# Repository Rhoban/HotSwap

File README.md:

# Hot swap

This is a simple hot swap board for dynamixel

## Features

With this system, when a battery is plugged, the LOGIC (for instance the robot computer) is powered through a diode, allowing a second battery to be plugged simultaneously

The SPDT switch allow to choose which battery is powering the motors, allowing an hot swap of the battery with the following sequence:

* Plugging the second battery
* Switching the SPDT switch
* Unplugging the first battery

The robot's computer will not reboot and the motors are now powered by the new battery

## 3 buses wiring

This Dynamixel HUB features 8 connectors, which have the same power supply but separated buses, with purpose to be combined with triple buses [Rhoban DXLBoard](http://github.com/Rhoban/DXLBoard):

* 2 connectors for leg 1
    * One should be connected to the first bus of the DXLBoard
    * The other should be connected to the first motor of one leg (the other are daisy chained)
* 4 connectors for the torso
    * One is connected to the second bus of the DXLBoard
    * The second to the first motor of left shoulder
    * The third to the first motor of right shoulder
    * The last to the first motor of the head
* 2 connectors for leg 2
    * One is connected to the second bus of DXLBoard
    * The other is connected to the other leg first mother

Then, the motors should be dispatched on three separate bus, one for left leg, one for right leg and one for the upper body of the robot.

## Components

You can find all the required components in the ``BOM.xlsx`` file. Note that you should choose between 3 and 4 pins for your dynamixel connectors.

* Switch
    * https://fr.farnell.com/arcolectric/c1520ataaa/interrupteur-a-bascule-spdt-ctr/dp/150551
    * Farnell ref: 150551
    * Constructor ref: C1520ATAAA 
* Double diode
    * https://fr.farnell.com/on-semiconductor/mbr1545ctg/diode-schottky-15a-45v-to-220/dp/1431049
    * Farnell ref: 1431049
    * Constructor ref: MBR1545CTG
* Dynamixel MOLEX connectors
    * 3 pins: https://fr.farnell.com/molex/22-03-5035/embase-droite-2-5mm-3-voies/dp/9979620
    * Farnell ref: 9979620
    * Constructor ref: 22-03-5035 
    * 4 pins: https://fr.farnell.com/molex/22035045/embase-vertical-2-5mm-4-voies/dp/1104204
    * Farnell ref: 1104204
    * Constructor ref: 22035045

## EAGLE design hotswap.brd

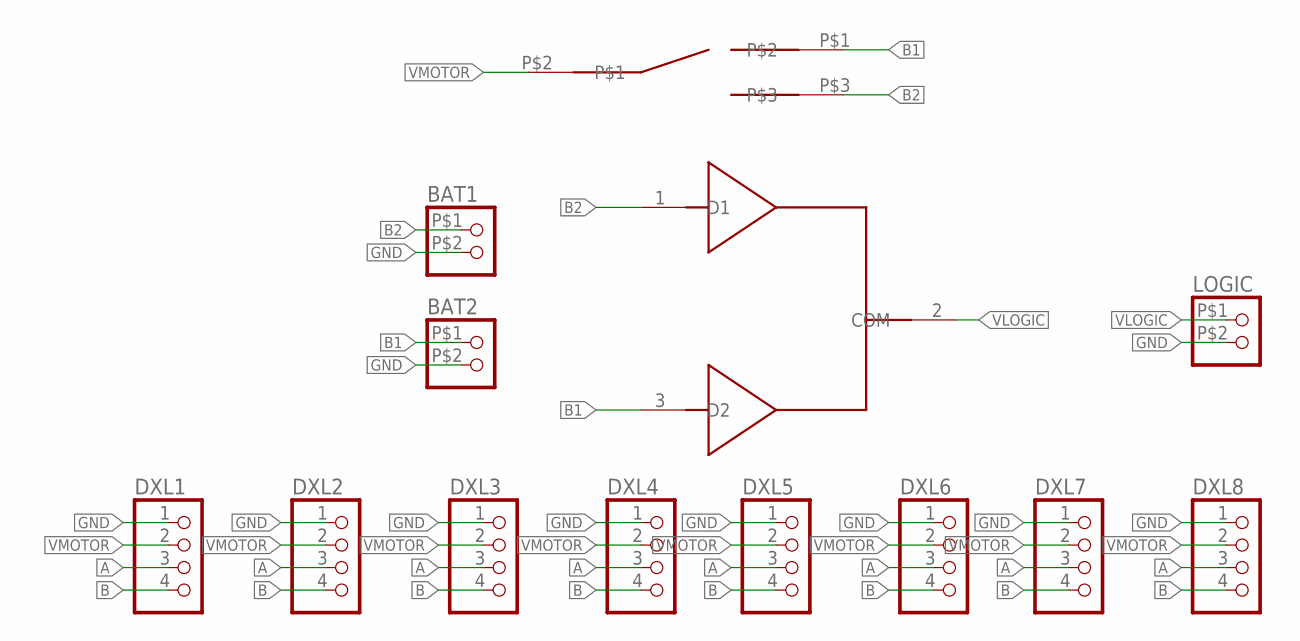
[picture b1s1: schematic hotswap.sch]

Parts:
BAT1, BAT2: CONNEC_1X02BIG; CONNEC_1X02_BIG
DXL1, DXL2, DXL3, DXL4, DXL5, DXL6, DXL7, DXL8: CONNEC_1X04; FARNELL 9979620 OR 1104204
LOGIC: CONNEC_1X02BIG; CONNEC_1X02_BIG
U$1: MBR1545CTG; TO-220-ALT; FARNELL 1431049
U$2: BIG_SPDT; FARNELL 150551

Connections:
A: DXL1.3, DXL2.3, DXL3.3, DXL4.3, DXL5.3, DXL6.3, DXL7.3, DXL8.3
B: DXL1.4, DXL2.4, DXL3.4, DXL4.4, DXL5.4, DXL6.4, DXL7.4, DXL8.4
B1: BAT2.P$1 (1), U$1.3 (D2), U$2.P$1
B2: BAT1.P$1 (1), U$1.1 (D1), U$2.P$3
GND: BAT1.P$2 (2), BAT2.P$2 (2), DXL1.1, DXL2.1, DXL3.1, DXL4.1, DXL5.1, DXL6.1, DXL7.1, DXL8.1, LOGIC.P$2 (2)
VLOGIC: LOGIC.P$1 (1), U$1.2 (COM)
VMOTOR: DXL1.2, DXL2.2, DXL3.2, DXL4.2, DXL5.2, DXL6.2, DXL7.2, DXL8.2, U$2.P$2

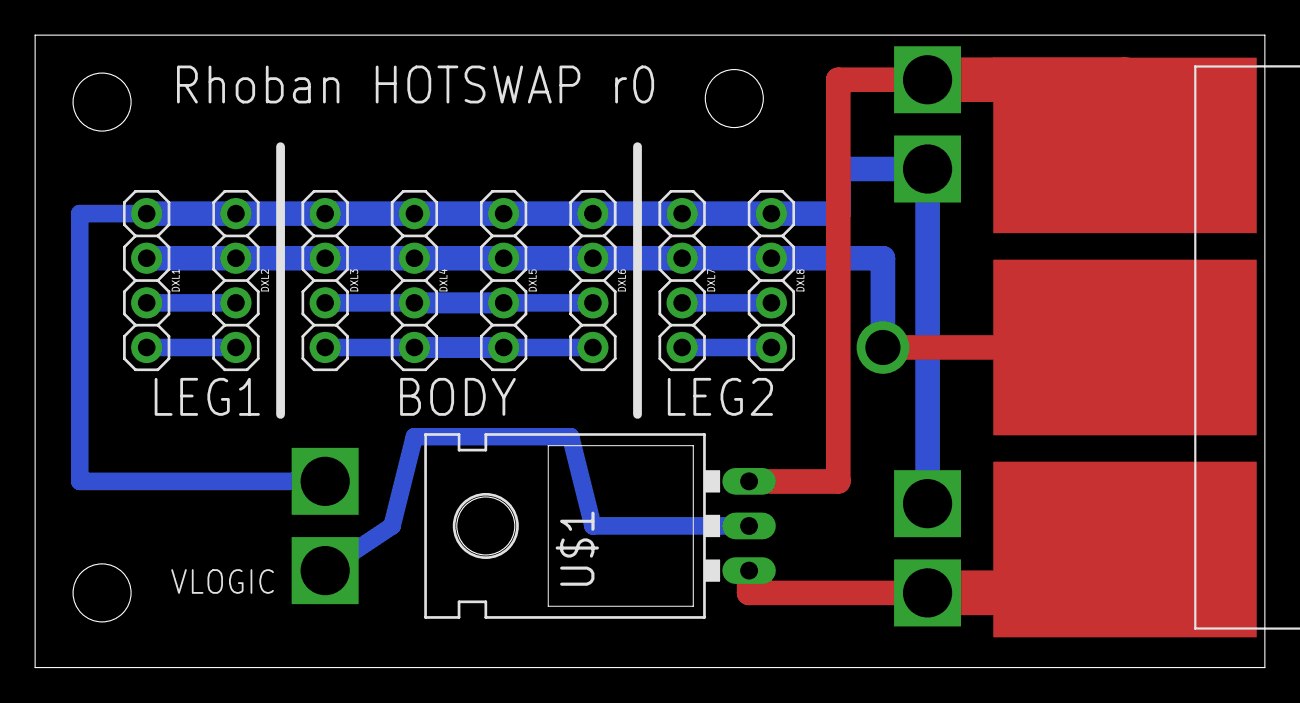
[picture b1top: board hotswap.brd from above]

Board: 2 copper layers, 70.0 x 36.0 mm, 16 parts (0 on the bottom side), 7 nets.

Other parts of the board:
U$3, U$4, U$5: STAND-OFF

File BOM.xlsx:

|  |  | Rhoban HotSwap Board Bill of materials
Item # | *Ref Des | *Qty | Manufacturer | *Mfg Part # | Description / Value | *Package | Type | Your Instructions / Notes
2 | DXL1, DXL2, DXL3, DXL4, DXL5, DXL6, DXL7, DXL8 | 8 | MOLEX | 22-03-5035 (3 PIN) OR 22-03-5045 (4 PIN) | Connector | - | Thru-Hole | Farnell : 9979620 OR 1104204
3 | U$1 | 1 | ON SEMICONDUCTOR | MBR1545CTG | Double Diode | TO-220 | Thru-Hole | Farnell : 1431049
4 | U$2 | 1 | ARCOELECTRIC | C1520ATAAA | SPDT Switch | - | Thru-Hole | Farnell : 150551
Click for Instructions on How to Create a BOM

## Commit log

2018-08-10 Hot swap
2018-08-10 README
2018-08-30 Fixing FARNELL attributes and writing BOM
2018-08-30 Fixing item #
2018-08-30 Documentation
2018-10-29 Gerber

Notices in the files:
parts and their libraries:
SparkFun-Electromechanical: Licensing: Creative Commons ShareAlike 4.0 International - https://creativecommons.org/licenses/by-sa/4.0
